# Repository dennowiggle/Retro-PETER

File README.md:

# Retro-PETER
A Retro computer project => FPGA peripheral board + 3.3V RCBUS slot + CPU board(s) making a custom system.

## Description
Retro-PETER is a family of boards based around the Lattice ECP5 FPGA to create a custom retro computer system.
* [PETER](Hardware/PETER "Peripheral ECP5 Technology and Entertainment Resource board.") base board with FPGA provides the peripheral features. It has on board SRAM memory but no CPU.
    - One 3.3V RCBUS connector provides a CPU slot.
    - One 3.3V RCBUS expansion connector allows connection of an RCBUS backplane for more card slots.
* [ANALYZER](Hardware/Analyzer "Logic Analyzer for RCBUS using PI PICO 2") is a 5V tolerant 72 channel logic analyzer for RCBUS.
* [BALD](Hardware/BALD "Bus Activity LED Display.") is an RCBUS LED card that flickers lights when there is activity. I found this useful for bringup of new CPU's either on an RCBUS CPU card or internal CPU cores.
* [BUTLER](Hardware/BUTLER "Backplane with Universal Translation Logic for Exploring Retro") is a backplane with voltage translation logic to support 2 x 3.3V connectors for 3.3V RCBUS cards and 3 x 5V connectors for 5V RCBUS cards.
* [GOLD](Hardware/GOLD "GPIO On LED Display.") is a simple LED board that connects to 6 GPIO outputs for flashing lights and debug info. I love a binary counter.
* [RANDY](Hardware/RANDY "RCBUS Adapter to Nouveau Design. Yeah!") is a bus adapter from RCBUS to John's Basement [2067-Z8S180](https://github.com/johnwinans/2067-Z8S180/) card.
* [SEWER](Hardware/SEWER "Simple Eval With EZ80F91 on RCBUS") is an eZ80 CPU card.
* [SPIFEE](Hardware/SPIFEE "Sixty-eight thousand Processor Including Flash Engineering Eval") is an RCBUS board with an M68SEC000FU20 CPU that runs in 8-bit mode.
* [ZORO](Hardware/ZORO "Z8S180 On RCBUS Only.") is a Z180 RCBUS CPU card.

**WARNING** : This is a 3.3V system and any connections to PETER, including RCBUS, must NOT exceed 3.3V.

**Disclaimer** This is a hobby project and a vehicle for play. Not intended to be a product or to be optimised for size, cost, function, or meet any standard. All boards are prototypes and should be considered such even if there are new revisions over time.

## Background
John Winans has a video series and boards for an ice40HX4K + Z180 CPU card aka Z80 Nouveau. There is also a companion CP/M video series and project files. This project grew from following along with those video's and projects. Here are some links to follow John's work :
* John's Basement [FPGA](https://www.youtube.com/playlist?list=PL3by7evD3F52On-ws9pcdQuEL-rYbNNFB) YouTube series.
    - Supporting  [2057-ice40HX4K](https://github.com/johnwinans/2057-ICE40HX4K-TQ144-breakout) board.
    - [Code](https://github.com/johnwinans/Verilog-Examples) for Series.
* John's Basement [Z80 Nouveau](https://www.youtube.com/playlist?list=PL3by7evD3F52rUbThUNDYGxNpKFF1HCNT) YouTube series.
    - Supporting [2067-Z8S180](https://github.com/johnwinans/2067-Z8S180/) board.
    - [Code](https://github.com/johnwinans/2067-Z8S180/tree/main/fpga) for Series.
* John's Basement [Z80 Retro](https://www.youtube.com/playlist?list=PL3by7evD3F51Cf9QnsAEdgSQ4cz7HQZX5) YouTube series covering CP/M.
    - [CP/M SW](https://github.com/Z80-Retro/2063-Z80-cpm) to go along with the video series and which supports 2057-ice40HX4K + 2067-Z8S180 aka Z80 Nouveau.
* Johns Z80 Retro! [Discord](https://discord.gg/jf73DRZvh5) channel.

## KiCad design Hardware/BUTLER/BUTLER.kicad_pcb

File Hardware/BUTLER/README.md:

# BUTLER
Backplane with Universal Translation Logic for Exploring Retro

## Description
BUTLER is an RCBUS backplane board with voltage translation logic. It has 2 connectors for 3.3V cards and 3 connectors for 5V cards.

The buffer direction control signal comes from the [PETER](../PETER) FPGA. The card uses three backplane signals for GND as well as GND planes to try and improve signal integrity.

## Top View

## Bottom View

## BUTLER Board Rev 0.0 Release Notes
1. The [output](output/) directory contains the BOM, netlist, and PDF schematic.

2. Board design used KiCad 9.0

## BUTLER Future Changes.
1. Replace U505 5V LDO with TRACO POWER TSR 1-2450 or equivalent that has a wide input voltage operating range and is a switch mode power supply. This has been tested on the prototype as rework and worked well.

## Notes
Only preliminary testing has taken place.

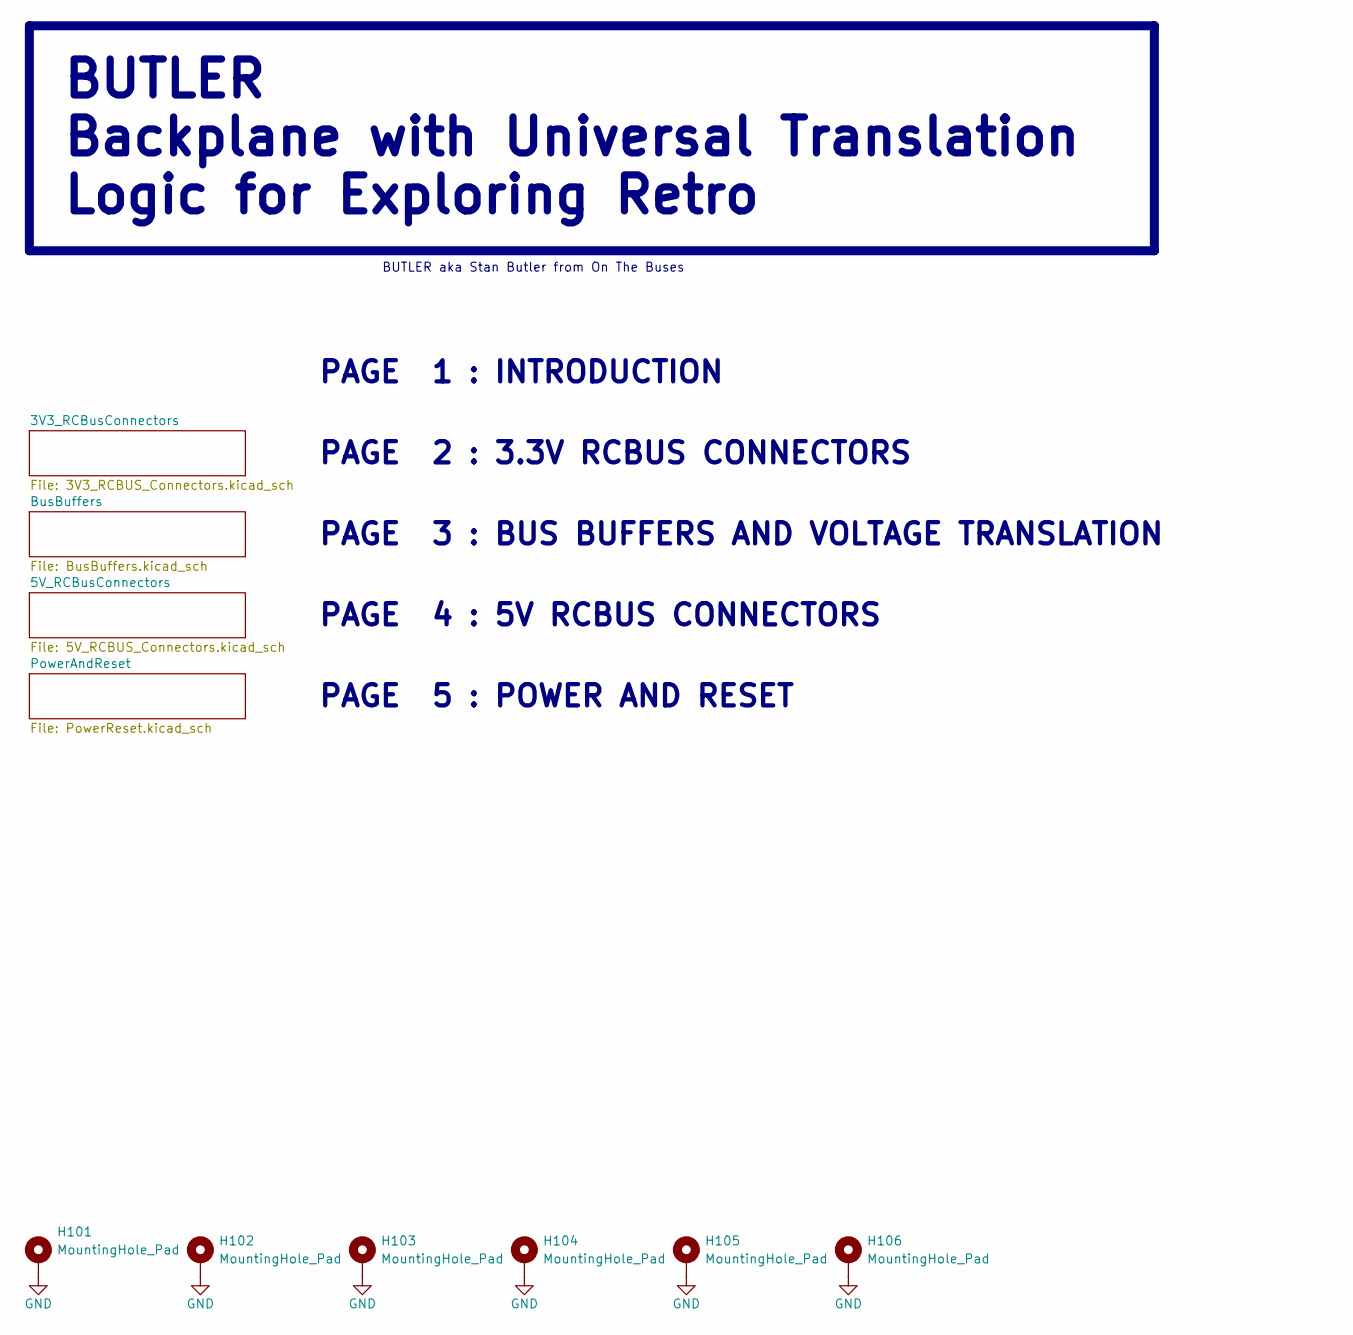
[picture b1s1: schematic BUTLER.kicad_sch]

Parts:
H101, H102, H103, H104, H105, H106: MountingHole_Pad; MountingHole_3.2mm_M3_DIN965_Pad

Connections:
GND: H101.1, H102.1, H103.1, H104.1, H105.1, H106.1; also elsewhere on the board

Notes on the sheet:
PAGE 5 : POWER AND RESET
PAGE 1 : INTRODUCTION
PAGE 4 : 5V RCBUS CONNECTORS
PAGE 2 : 3.3V RCBUS CONNECTORS
BUTLER aka Stan Butler from On The Buses
PAGE 3 : BUS BUFFERS AND VOLTAGE TRANSLATION
BUTLER Backplane with Universal Translation Logic for Exploring Retro

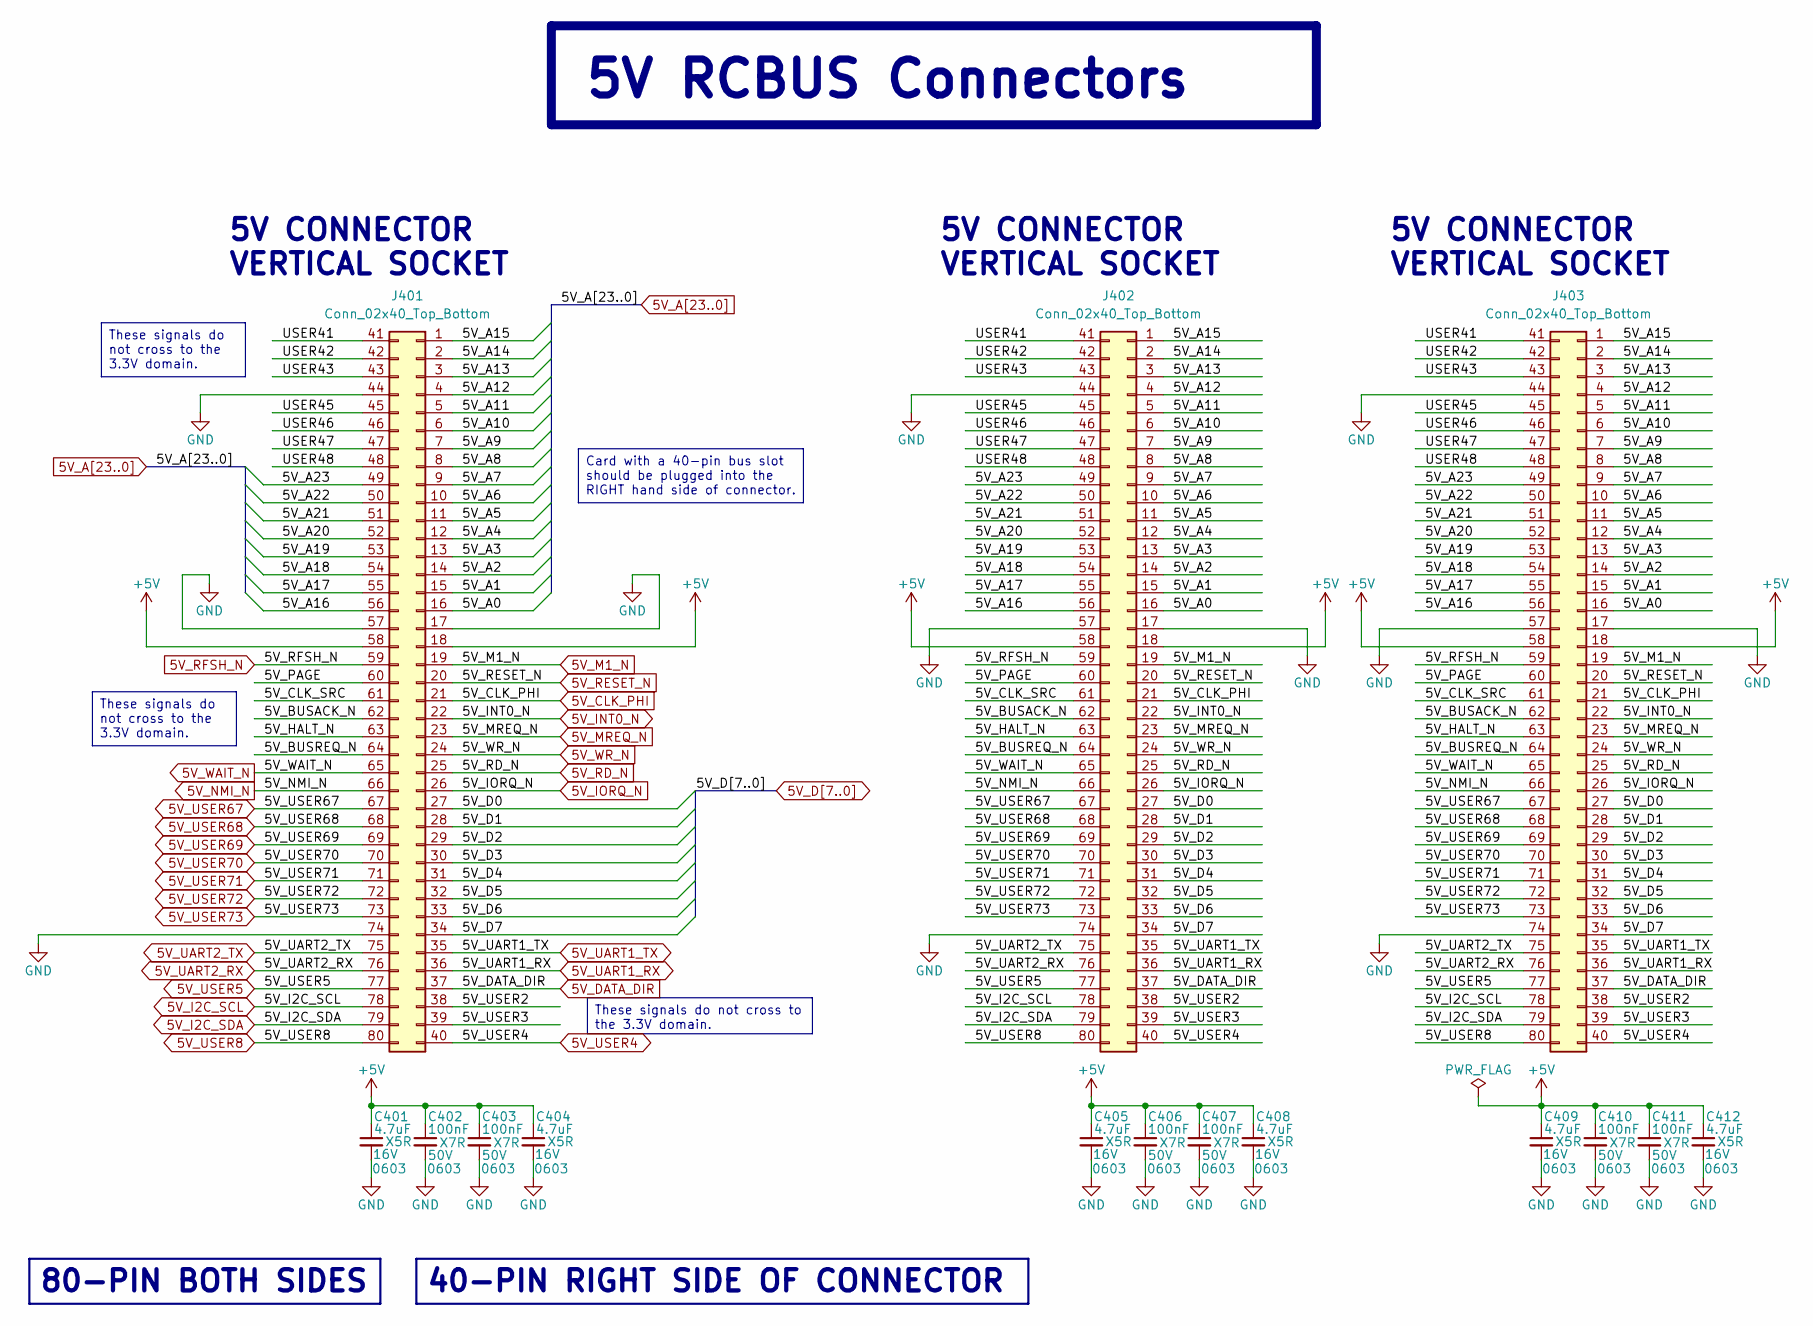
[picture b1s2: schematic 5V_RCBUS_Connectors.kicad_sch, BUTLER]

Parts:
C401, C404, C405, C408, C409, C412: 4.7uF; C_0603_1608Metric; Voltage 16V; Tolerance 10%; MPN CL10A475KO8NNNC; Digikey 1276-1784-1-ND
C402, C403, C406, C407, C410, C411: 100nF; C_0603_1608Metric; Voltage 50V; Tolerance 10%; MPN CC0603KRX7R9BB104; Digikey 311-1344-1-ND
J401, J402, J403: Conn_02x40_Top_Bottom; PinSocket_2x40_P2.54mm_Vertical_RCBUS80; LCSC Part # C7500806

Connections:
5V_A0: J401.16, J402.16, J403.16; also elsewhere on the board
5V_A1: J401.15, J402.15, J403.15; also elsewhere on the board
5V_A2: J401.14, J402.14, J403.14; also elsewhere on the board
5V_A3: J401.13, J402.13, J403.13; also elsewhere on the board
5V_A4: J401.12, J402.12, J403.12; also elsewhere on the board
5V_A5: J401.11, J402.11, J403.11; also elsewhere on the board
5V_A6: J401.10, J402.10, J403.10; also elsewhere on the board
5V_A7: J401.9, J402.9, J403.9; also elsewhere on the board
5V_A8: J401.8, J402.8, J403.8; also elsewhere on the board
5V_A9: J401.7, J402.7, J403.7; also elsewhere on the board
5V_A10: J401.6, J402.6, J403.6; also elsewhere on the board
5V_A11: J401.5, J402.5, J403.5; also elsewhere on the board
5V_A12: J401.4, J402.4, J403.4; also elsewhere on the board
5V_A13: J401.3, J402.3, J403.3; also elsewhere on the board
5V_A14: J401.2, J402.2, J403.2; also elsewhere on the board
5V_A15: J401.1, J402.1, J403.1; also elsewhere on the board
5V_A16: J401.56, J402.56, J403.56; also elsewhere on the board
5V_A17: J401.55, J402.55, J403.55; also elsewhere on the board
5V_A18: J401.54, J402.54, J403.54; also elsewhere on the board
5V_A19: J401.53, J402.53, J403.53; also elsewhere on the board
5V_A20: J401.52, J402.52, J403.52; also elsewhere on the board
5V_A21: J401.51, J402.51, J403.51; also elsewhere on the board
5V_A22: J401.50, J402.50, J403.50; also elsewhere on the board
5V_A23: J401.49, J402.49, J403.49; also elsewhere on the board
5V_CLK_PHI: J401.21, J402.21, J403.21; also elsewhere on the board
5V_D0: J401.27, J402.27, J403.27; also elsewhere on the board
5V_D1: J401.28, J402.28, J403.28; also elsewhere on the board
5V_D2: J401.29, J402.29, J403.29; also elsewhere on the board
5V_D3: J401.30, J402.30, J403.30; also elsewhere on the board
5V_D4: J401.31, J402.31, J403.31; also elsewhere on the board
5V_D5: J401.32, J402.32, J403.32; also elsewhere on the board
5V_D6: J401.33, J402.33, J403.33; also elsewhere on the board
5V_D7: J401.34, J402.34, J403.34; also elsewhere on the board
5V_DATA_DIR: J401.37, J402.37, J403.37; also elsewhere on the board
5V_I2C_SCL: J401.78, J402.78, J403.78; also elsewhere on the board
5V_I2C_SDA: J401.79, J402.79, J403.79; also elsewhere on the board
5V_INT0_N: J401.22, J402.22, J403.22; also elsewhere on the board
5V_IORQ_N: J401.26, J402.26, J403.26; also elsewhere on the board
5V_M1_N: J401.19, J402.19, J403.19; also elsewhere on the board
5V_MREQ_N: J401.23, J402.23, J403.23; also elsewhere on the board
5V_NMI_N: J401.66, J402.66, J403.66; also elsewhere on the board
5V_RD_N: J401.25, J402.25, J403.25; also elsewhere on the board
5V_RESET_N: J401.20, J402.20, J403.20; also elsewhere on the board
5V_RFSH_N: J401.59, J402.59, J403.59; also elsewhere on the board
5V_UART1_RX: J401.36, J402.36, J403.36; also elsewhere on the board
5V_UART1_TX: J401.35, J402.35, J403.35; also elsewhere on the board
5V_UART2_RX: J401.76, J402.76, J403.76; also elsewhere on the board
5V_UART2_TX: J401.75, J402.75, J403.75; also elsewhere on the board
5V_USER4: J401.40, J402.40, J403.40; also elsewhere on the board
5V_USER5: J401.77, J402.77, J403.77; also elsewhere on the board
5V_USER8: J401.80, J402.80, J403.80; also elsewhere on the board
5V_USER67: J401.67, J402.67, J403.67; also elsewhere on the board
5V_USER68: J401.68, J402.68, J403.68; also elsewhere on the board
5V_USER69: J401.69, J402.69, J403.69; also elsewhere on the board
5V_USER70: J401.70, J402.70, J403.70; also elsewhere on the board
5V_USER71: J401.71, J402.71, J403.71; also elsewhere on the board
5V_USER72: J401.72, J402.72, J403.72; also elsewhere on the board
5V_USER73: J401.73, J402.73, J403.73; also elsewhere on the board
5V_WAIT_N: J401.65, J402.65, J403.65; also elsewhere on the board
5V_WR_N: J401.24, J402.24, J403.24; also elsewhere on the board
+5V: C401.1, C402.1, C403.1, C404.1, C405.1, C406.1, C407.1, C408.1, C409.1, C410.1, C411.1, C412.1, J401.18, J401.58, J402.18, J402.58, J403.18, J403.58; also elsewhere on the board
/5V_RCBusConnectors/5V_BUSACK_N: J401.62, J402.62, J403.62
/5V_RCBusConnectors/5V_BUSREQ_N: J401.64, J402.64, J403.64
/5V_RCBusConnectors/5V_CLK_SRC: J401.61, J402.61, J403.61
/5V_RCBusConnectors/5V_HALT_N: J401.63, J402.63, J403.63
/5V_RCBusConnectors/5V_PAGE: J401.60, J402.60, J403.60
/5V_RCBusConnectors/5V_USER2: J401.38, J402.38, J403.38
/5V_RCBusConnectors/5V_USER3: J401.39, J402.39, J403.39
/5V_RCBusConnectors/USER41: J401.41, J402.41, J403.41
/5V_RCBusConnectors/USER42: J401.42, J402.42, J403.42
/5V_RCBusConnectors/USER43: J401.43, J402.43, J403.43
/5V_RCBusConnectors/USER45: J401.45, J402.45, J403.45
/5V_RCBusConnectors/USER46: J401.46, J402.46, J403.46
/5V_RCBusConnectors/USER47: J401.47, J402.47, J403.47
/5V_RCBusConnectors/USER48: J401.48, J402.48, J403.48
GND: C401.2, C402.2, C403.2, C404.2, C405.2, C406.2, C407.2, C408.2, C409.2, C410.2, C411.2, C412.2, J401.17, J401.44, J401.57, J401.74, J402.17, J402.44, J402.57, J402.74, J403.17, J403.44, J403.57, J403.74; also elsewhere on the board

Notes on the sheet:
80-PIN BOTH SIDES
40-PIN RIGHT SIDE OF CONNECTOR
5V CONNECTOR VERTICAL SOCKET
Card with a 40-pin bus slot should be plugged into the RIGHT hand side of connector.
These signals do not cross to the 3.3V domain.
5V RCBUS Connectors

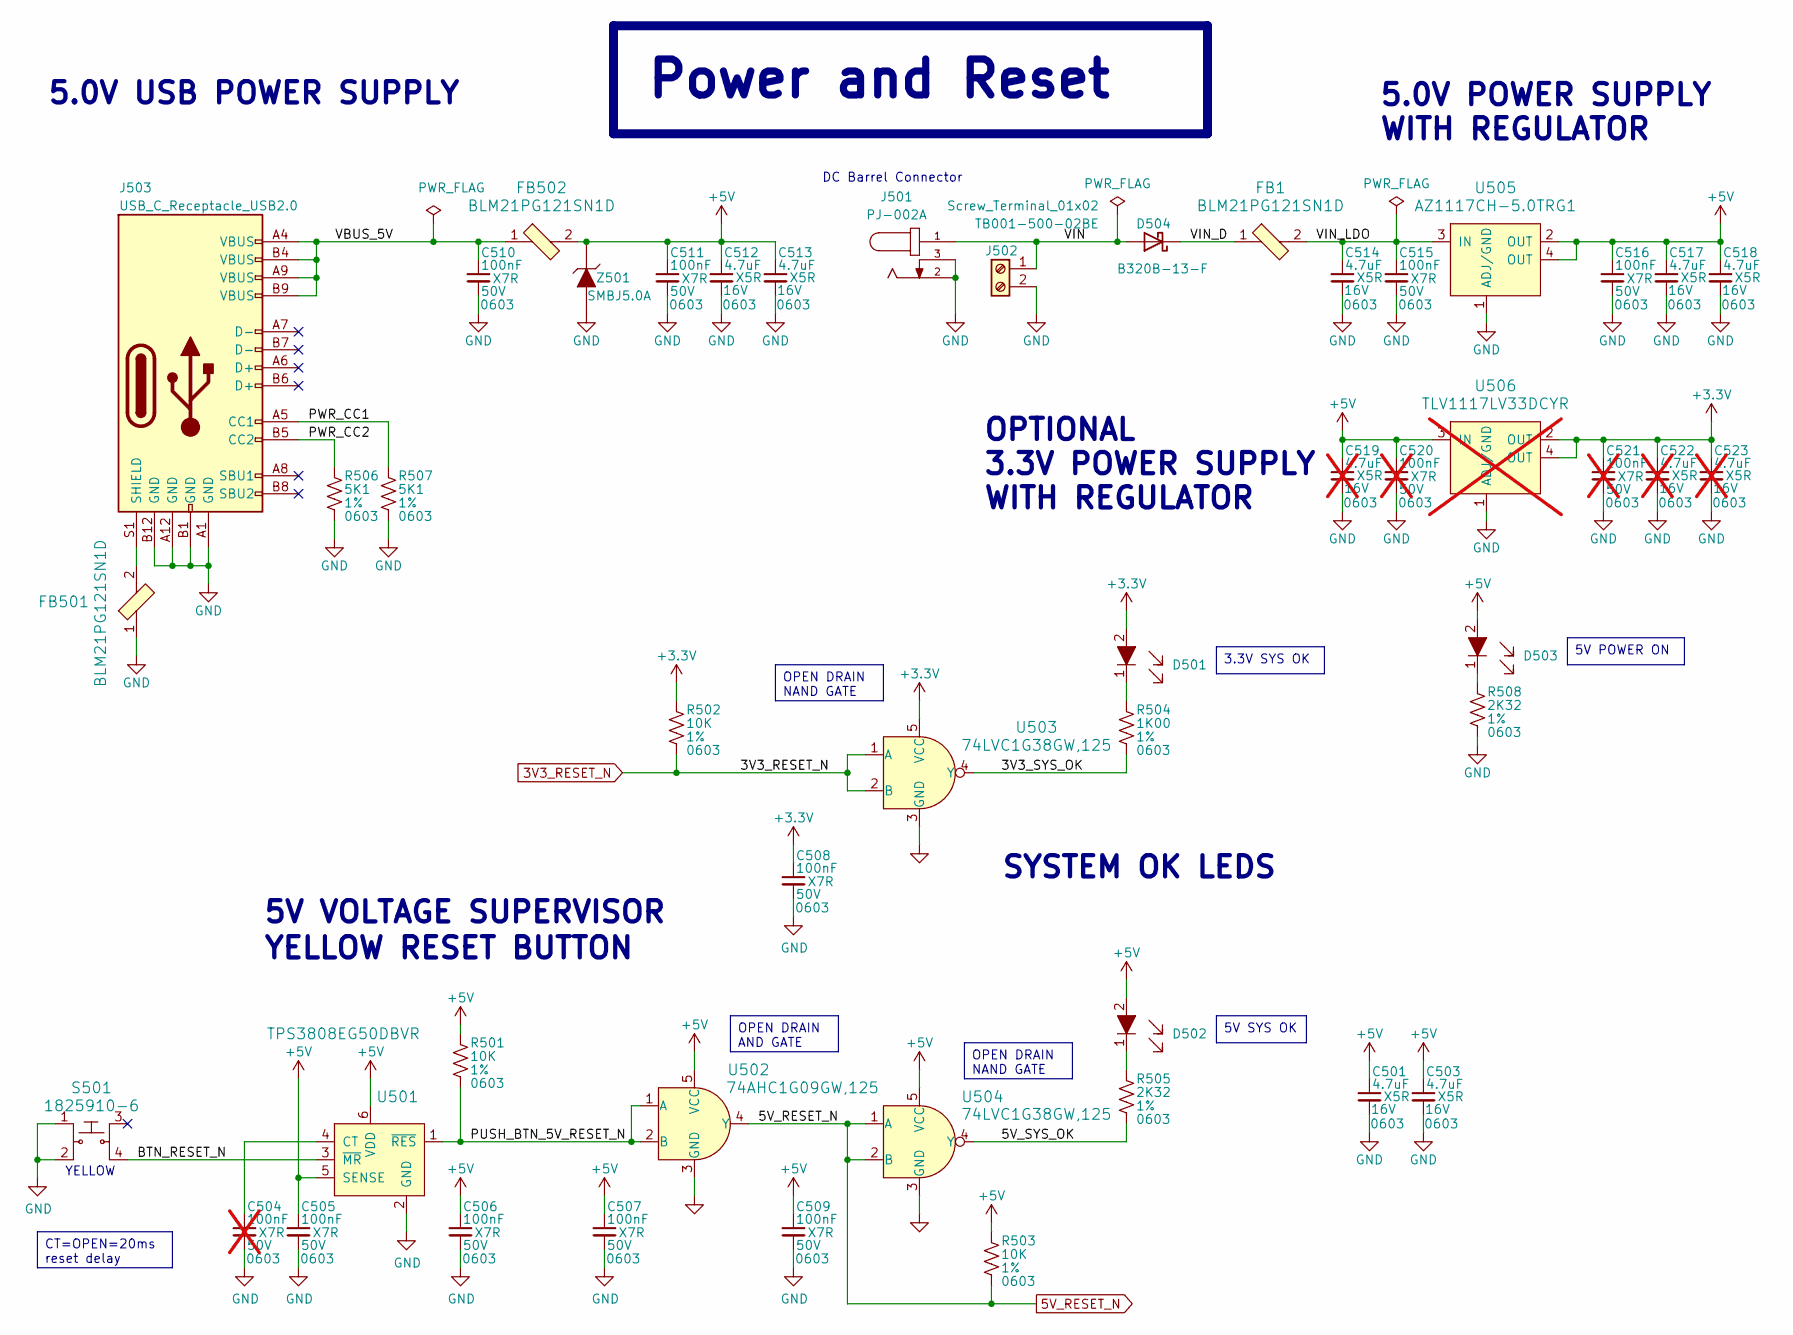
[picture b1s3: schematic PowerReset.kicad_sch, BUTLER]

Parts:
C501, C503, C512, C513, C514, C517, C518: 4.7uF; C_0603_1608Metric; Voltage 16V; Tolerance 10%; MPN CL10A475KO8NNNC; Digikey 1276-1784-1-ND
C504, C520, C521: 100nF; C_0603_1608Metric; Voltage 50V; Tolerance 10%; MPN CC0603KRX7R9BB104; Digikey 311-1344-1-ND; not fitted
C505, C506, C507, C508, C509, C510, C511, C515, C516: 100nF; C_0603_1608Metric; Voltage 50V; Tolerance 10%; MPN CC0603KRX7R9BB104; Digikey 311-1344-1-ND
C519, C522, C523: 4.7uF; C_0603_1608Metric; Voltage 16V; Tolerance 10%; MPN CL10A475KO8NNNC; Digikey 1276-1784-1-ND; not fitted
D501, D502, D503: LED_LTST-S270KGKT; LTST-S270KGKT; MPN LTST-S270KGKT; Digikey 160-1478-1-ND
D504: B320B-13-F; D_SMB; MPN B320B-13-F; Digikey B320B-FDICT-ND
FB1, FB501, FB502: BLM21PG121SN1D; L_0805_2012Metric; MPN BLM21PG121SN1D; Digikey 490-5986-1-ND
J501: PJ-002A; CUI_PJ-002A; MPN PJ-002A; Digikey CP-002A-ND
J502: Screw_Terminal_01x02; CUI_TB001-500-02BE; MPN TB001-500-02BE; Digikey 102-6134-ND
J503: USB_C_Receptacle_USB2.0; USB_C_Receptacle_HRO_TYPE-C-31-M-12; MPN USB4105-GF-A; LCSC Part # C167321
R501, R502, R503: 10K; R_0603_1608Metric; Tolerance 1%; MPN RC0603FR-0710KL; Digikey 311-10.0KHRCT-ND
R504: 1K00; R_0603_1608Metric; Tolerance 1%; MPN RC0603FR-071KL; Digikey 311-1.00KHRCT-ND
R505, R508: 2K32; R_0603_1608Metric; Tolerance 1%; MPN RC0603FR-072K32L; Digikey 311-2.32KHRCT-ND
R506, R507: 5K1; R_0603_1608Metric; Tolerance 1%; MPN RC0603FR-075K1L; Digikey 311-5.10KHRCT-ND
S501: 1825910-6; Switch_Tactile_THT_6x6mm; MPN 1825910-6; Digi-Key_PN 450-1650-ND
U501: TPS3808EG50DBVR; TSOT-23-6_HandSoldering; MPN TPS3808EG50DBVR; Digikey 296-TPS3808EG50DBVRCT-ND
U502: 74AHC1G09GW,125; SOT-353_SC-70-5; MPN 74AHC1G09GW,125; Digikey 1727-6017-1-ND
U503, U504: 74LVC1G38GW,125; SOT-353_SC-70-5; MPN 74LVC1G38GW,125; Digikey 1727-6077-1-ND
U505: AZ1117CH-5.0TRG1; SOT-223; MPN AZ1117CH-5.0TRG1; Digikey AZ1117CH-5.0TRG1DICT-ND
U506: TLV1117LV33DCYR; SOT-223; MPN TLV1117LV33DCYR; Digikey 296-28778-1-ND; not fitted
Z501: SMBJ5.0A; D_SMB; MPN SMBJ5.0A; Digikey SMBJ5.0ALFCT-ND

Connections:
3V3_RESET_N: R502.2, U503.1 (A), U503.2 (B); also elsewhere on the board
5V_RESET_N: R503.2, U502.4 (Y), U504.1 (A), U504.2 (B); also elsewhere on the board
+3.3V: C508.1, C521.1, C522.1, C523.1, D501.2, R502.1, U503.5 (VCC), U506.2 (OUT), U506.4 (OUT); also elsewhere on the board
+5V: C501.1, C503.1, C505.1, C506.1, C507.1, C509.1, C511.1, C512.1, C513.1, C516.1, C517.1, C518.1, C519.1, C520.1, D502.2, D503.2, FB502.2, R501.1, R503.1, U501.5 (SENSE), U501.6 (VDD), U502.5 (VCC), U504.5 (VCC), U505.2 (OUT), U505.4 (OUT), U506.3 (IN), Z501.1; also elsewhere on the board
/PowerAndReset/3V3_SYS_OK: R504.2, U503.4 (Y)
/PowerAndReset/5V_SYS_OK: R505.2, U504.4 (Y)
/PowerAndReset/BTN_RESET_N: S501.4, U501.3 (~MR)
/PowerAndReset/PUSH_BTN_5V_RESET_N: R501.2, U501.1 (~RES), U502.1 (A), U502.2 (B)
/PowerAndReset/PWR_CC1: J503.A5 (CC1), R507.1
/PowerAndReset/PWR_CC2: J503.B5 (CC2), R506.1
/PowerAndReset/VBUS_5V: C510.1, FB502.1, J503.A4 (VBUS), J503.A9 (VBUS), J503.B4 (VBUS), J503.B9 (VBUS)
/PowerAndReset/VIN: D504.2 (A), J501.1, J502.1
/PowerAndReset/VIN_D: D504.1 (K), FB1.1
/PowerAndReset/VIN_LDO: C514.1, C515.1, FB1.2, U505.3 (IN)
GND: C501.2, C503.2, C504.2, C505.2, C506.2, C507.2, C508.2, C509.2, C510.2, C511.2, C512.2, C513.2, C514.2, C515.2, C516.2, C517.2, C518.2, C519.2, C520.2, C521.2, C522.2, C523.2, FB501.1, J501.2, J501.3, J502.2, J503.A1 (GND), J503.A12 (GND), J503.B1 (GND), J503.B12 (GND), R506.2, R507.2, R508.2, S501.1, S501.2, U501.2 (GND), U502.3 (GND), U503.3 (GND), U504.3 (GND), U505.1 (ADJ/GND), U506.1 (ADJ/GND), Z501.2; also elsewhere on the board
unnamed: D501.1, R504.1
unnamed: D502.1, R505.1
unnamed: D503.1, R508.1
unnamed: FB501.2, J503.S1 (SHIELD)
unnamed: C504.1, U501.4 (CT)

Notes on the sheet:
5.0V USB POWER SUPPLY
OPTIONAL 3.3V POWER SUPPLY WITH REGULATOR
YELLOW RESET BUTTON
SYSTEM OK LEDS
5.0V POWER SUPPLY WITH REGULATOR
DC Barrel Connector
5V VOLTAGE SUPERVISOR
YELLOW
3.3V SYS OK
OPEN DRAIN NAND GATE
5V POWER ON
CT=OPEN=20ms reset delay
OPEN DRAIN AND GATE
5V SYS OK
Power and Reset

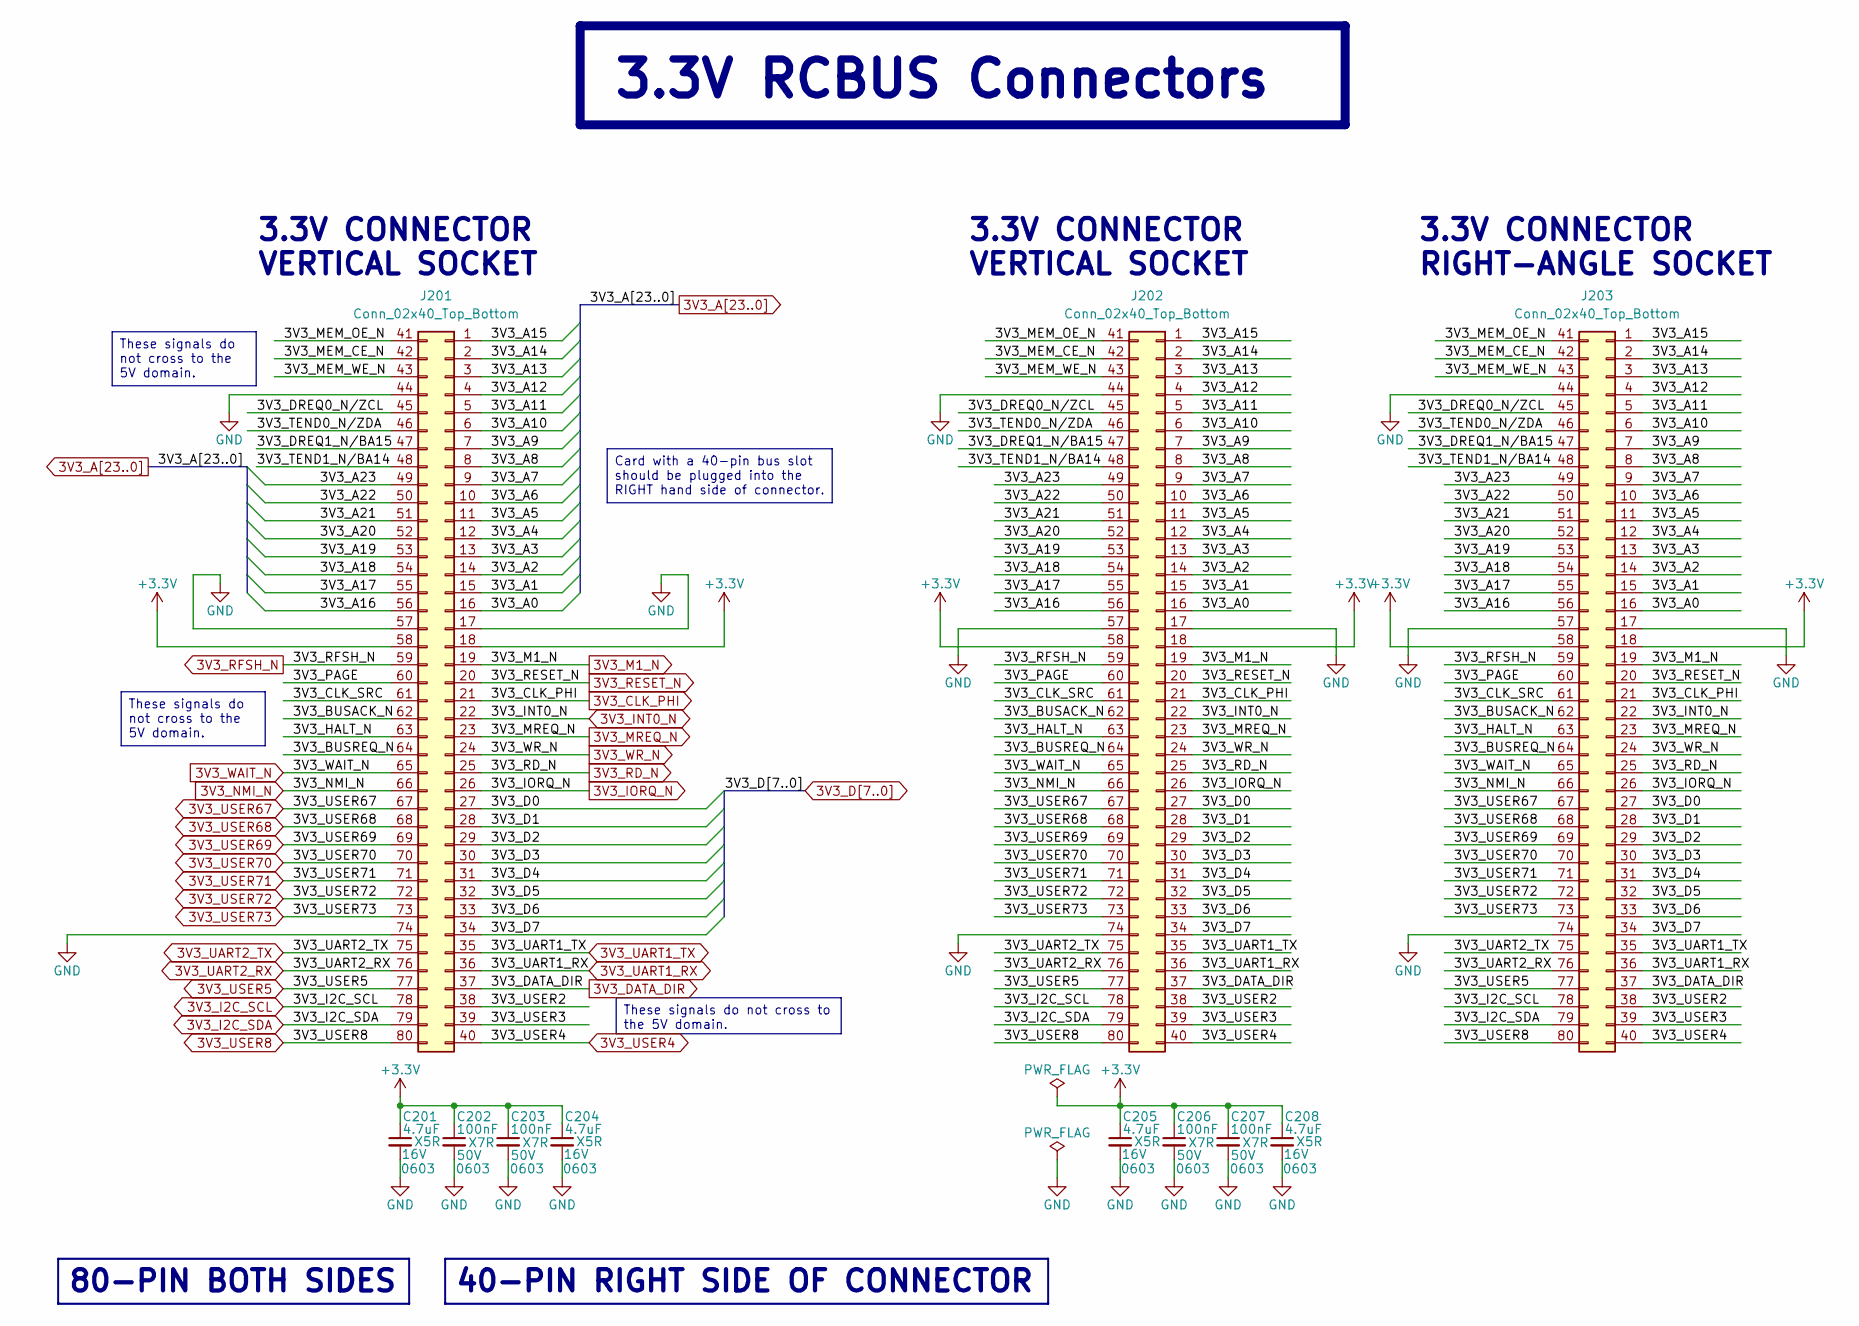
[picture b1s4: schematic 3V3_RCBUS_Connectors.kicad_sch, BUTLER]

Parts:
C201, C204, C205, C208: 4.7uF; C_0603_1608Metric; Voltage 16V; Tolerance 10%; MPN CL10A475KO8NNNC; Digikey 1276-1784-1-ND
C202, C203, C206, C207: 100nF; C_0603_1608Metric; Voltage 50V; Tolerance 10%; MPN CC0603KRX7R9BB104; Digikey 311-1344-1-ND
J201, J202: Conn_02x40_Top_Bottom; PinSocket_2x40_P2.54mm_Vertical_RCBUS80; LCSC Part # C7500806
J203: Conn_02x40_Top_Bottom; PinSocket_2x40_P2.54mm_Horizontal_RCBUS80; MPN SSW-140-02-T-D-RA; Digikey 612-SSW-140-02-T-D-RA-ND

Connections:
3V3_A0: J201.16, J202.16, J203.16; also elsewhere on the board
3V3_A1: J201.15, J202.15, J203.15; also elsewhere on the board
3V3_A2: J201.14, J202.14, J203.14; also elsewhere on the board
3V3_A3: J201.13, J202.13, J203.13; also elsewhere on the board
3V3_A4: J201.12, J202.12, J203.12; also elsewhere on the board
3V3_A5: J201.11, J202.11, J203.11; also elsewhere on the board
3V3_A6: J201.10, J202.10, J203.10; also elsewhere on the board
3V3_A7: J201.9, J202.9, J203.9; also elsewhere on the board
3V3_A8: J201.8, J202.8, J203.8; also elsewhere on the board
3V3_A9: J201.7, J202.7, J203.7; also elsewhere on the board
3V3_A10: J201.6, J202.6, J203.6; also elsewhere on the board
3V3_A11: J201.5, J202.5, J203.5; also elsewhere on the board
3V3_A12: J201.4, J202.4, J203.4; also elsewhere on the board
3V3_A13: J201.3, J202.3, J203.3; also elsewhere on the board
3V3_A14: J201.2, J202.2, J203.2; also elsewhere on the board
3V3_A15: J201.1, J202.1, J203.1; also elsewhere on the board
3V3_A16: J201.56, J202.56, J203.56; also elsewhere on the board
3V3_A17: J201.55, J202.55, J203.55; also elsewhere on the board
3V3_A18: J201.54, J202.54, J203.54; also elsewhere on the board
3V3_A19: J201.53, J202.53, J203.53; also elsewhere on the board
3V3_A20: J201.52, J202.52, J203.52; also elsewhere on the board
3V3_A21: J201.51, J202.51, J203.51; also elsewhere on the board
3V3_A22: J201.50, J202.50, J203.50; also elsewhere on the board
3V3_A23: J201.49, J202.49, J203.49; also elsewhere on the board
3V3_CLK_PHI: J201.21, J202.21, J203.21; also elsewhere on the board
3V3_D0: J201.27, J202.27, J203.27; also elsewhere on the board
3V3_D1: J201.28, J202.28, J203.28; also elsewhere on the board
3V3_D2: J201.29, J202.29, J203.29; also elsewhere on the board
3V3_D3: J201.30, J202.30, J203.30; also elsewhere on the board
3V3_D4: J201.31, J202.31, J203.31; also elsewhere on the board
3V3_D5: J201.32, J202.32, J203.32; also elsewhere on the board
3V3_D6: J201.33, J202.33, J203.33; also elsewhere on the board
3V3_D7: J201.34, J202.34, J203.34; also elsewhere on the board
3V3_DATA_DIR: J201.37, J202.37, J203.37; also elsewhere on the board
3V3_I2C_SCL: J201.78, J202.78, J203.78; also elsewhere on the board
3V3_I2C_SDA: J201.79, J202.79, J203.79; also elsewhere on the board
3V3_INT0_N: J201.22, J202.22, J203.22; also elsewhere on the board
3V3_IORQ_N: J201.26, J202.26, J203.26; also elsewhere on the board
3V3_M1_N: J201.19, J202.19, J203.19; also elsewhere on the board
3V3_MREQ_N: J201.23, J202.23, J203.23; also elsewhere on the board
3V3_NMI_N: J201.66, J202.66, J203.66; also elsewhere on the board
3V3_RD_N: J201.25, J202.25, J203.25; also elsewhere on the board
3V3_RESET_N: J201.20, J202.20, J203.20; also elsewhere on the board
3V3_RFSH_N: J201.59, J202.59, J203.59; also elsewhere on the board
3V3_UART1_RX: J201.36, J202.36, J203.36; also elsewhere on the board
3V3_UART1_TX: J201.35, J202.35, J203.35; also elsewhere on the board
3V3_UART2_RX: J201.76, J202.76, J203.76; also elsewhere on the board
3V3_UART2_TX: J201.75, J202.75, J203.75; also elsewhere on the board
3V3_USER4: J201.40, J202.40, J203.40; also elsewhere on the board
3V3_USER5: J201.77, J202.77, J203.77; also elsewhere on the board
3V3_USER8: J201.80, J202.80, J203.80; also elsewhere on the board
3V3_USER67: J201.67, J202.67, J203.67; also elsewhere on the board
3V3_USER68: J201.68, J202.68, J203.68; also elsewhere on the board
3V3_USER69: J201.69, J202.69, J203.69; also elsewhere on the board
3V3_USER70: J201.70, J202.70, J203.70; also elsewhere on the board
3V3_USER71: J201.71, J202.71, J203.71; also elsewhere on the board
3V3_USER72: J201.72, J202.72, J203.72; also elsewhere on the board
3V3_USER73: J201.73, J202.73, J203.73; also elsewhere on the board
3V3_WAIT_N: J201.65, J202.65, J203.65; also elsewhere on the board
3V3_WR_N: J201.24, J202.24, J203.24; also elsewhere on the board
+3.3V: C201.1, C202.1, C203.1, C204.1, C205.1, C206.1, C207.1, C208.1, J201.18, J201.58, J202.18, J202.58, J203.18, J203.58; also elsewhere on the board
/3V3_RCBusConnectors/3V3_BUSACK_N: J201.62, J202.62, J203.62
/3V3_RCBusConnectors/3V3_BUSREQ_N: J201.64, J202.64, J203.64
/3V3_RCBusConnectors/3V3_CLK_SRC: J201.61, J202.61, J203.61
/3V3_RCBusConnectors/3V3_DREQ0_N/ZCL: J201.45, J202.45, J203.45
/3V3_RCBusConnectors/3V3_DREQ1_N/BA15: J201.47, J202.47, J203.47
/3V3_RCBusConnectors/3V3_HALT_N: J201.63, J202.63, J203.63
/3V3_RCBusConnectors/3V3_MEM_CE_N: J201.42, J202.42, J203.42
/3V3_RCBusConnectors/3V3_MEM_OE_N: J201.41, J202.41, J203.41
/3V3_RCBusConnectors/3V3_MEM_WE_N: J201.43, J202.43, J203.43
/3V3_RCBusConnectors/3V3_PAGE: J201.60, J202.60, J203.60
/3V3_RCBusConnectors/3V3_TEND0_N/ZDA: J201.46, J202.46, J203.46
/3V3_RCBusConnectors/3V3_TEND1_N/BA14: J201.48, J202.48, J203.48
/3V3_RCBusConnectors/3V3_USER2: J201.38, J202.38, J203.38
/3V3_RCBusConnectors/3V3_USER3: J201.39, J202.39, J203.39
GND: C201.2, C202.2, C203.2, C204.2, C205.2, C206.2, C207.2, C208.2, J201.17, J201.44, J201.57, J201.74, J202.17, J202.44, J202.57, J202.74, J203.17, J203.44, J203.57, J203.74; also elsewhere on the board

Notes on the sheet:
80-PIN BOTH SIDES
40-PIN RIGHT SIDE OF CONNECTOR
3.3V CONNECTOR RIGHT-ANGLE SOCKET
3.3V CONNECTOR VERTICAL SOCKET
Card with a 40-pin bus slot should be plugged into the RIGHT hand side of connector.
These signals do not cross to the 5V domain.
3.3V RCBUS Connectors

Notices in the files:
Hardware/Analyzer/Analyzer.kicad_pcb:
Copyright © 2026
Hardware/BALD/BALD.kicad_pcb:
Copyright © 2024
